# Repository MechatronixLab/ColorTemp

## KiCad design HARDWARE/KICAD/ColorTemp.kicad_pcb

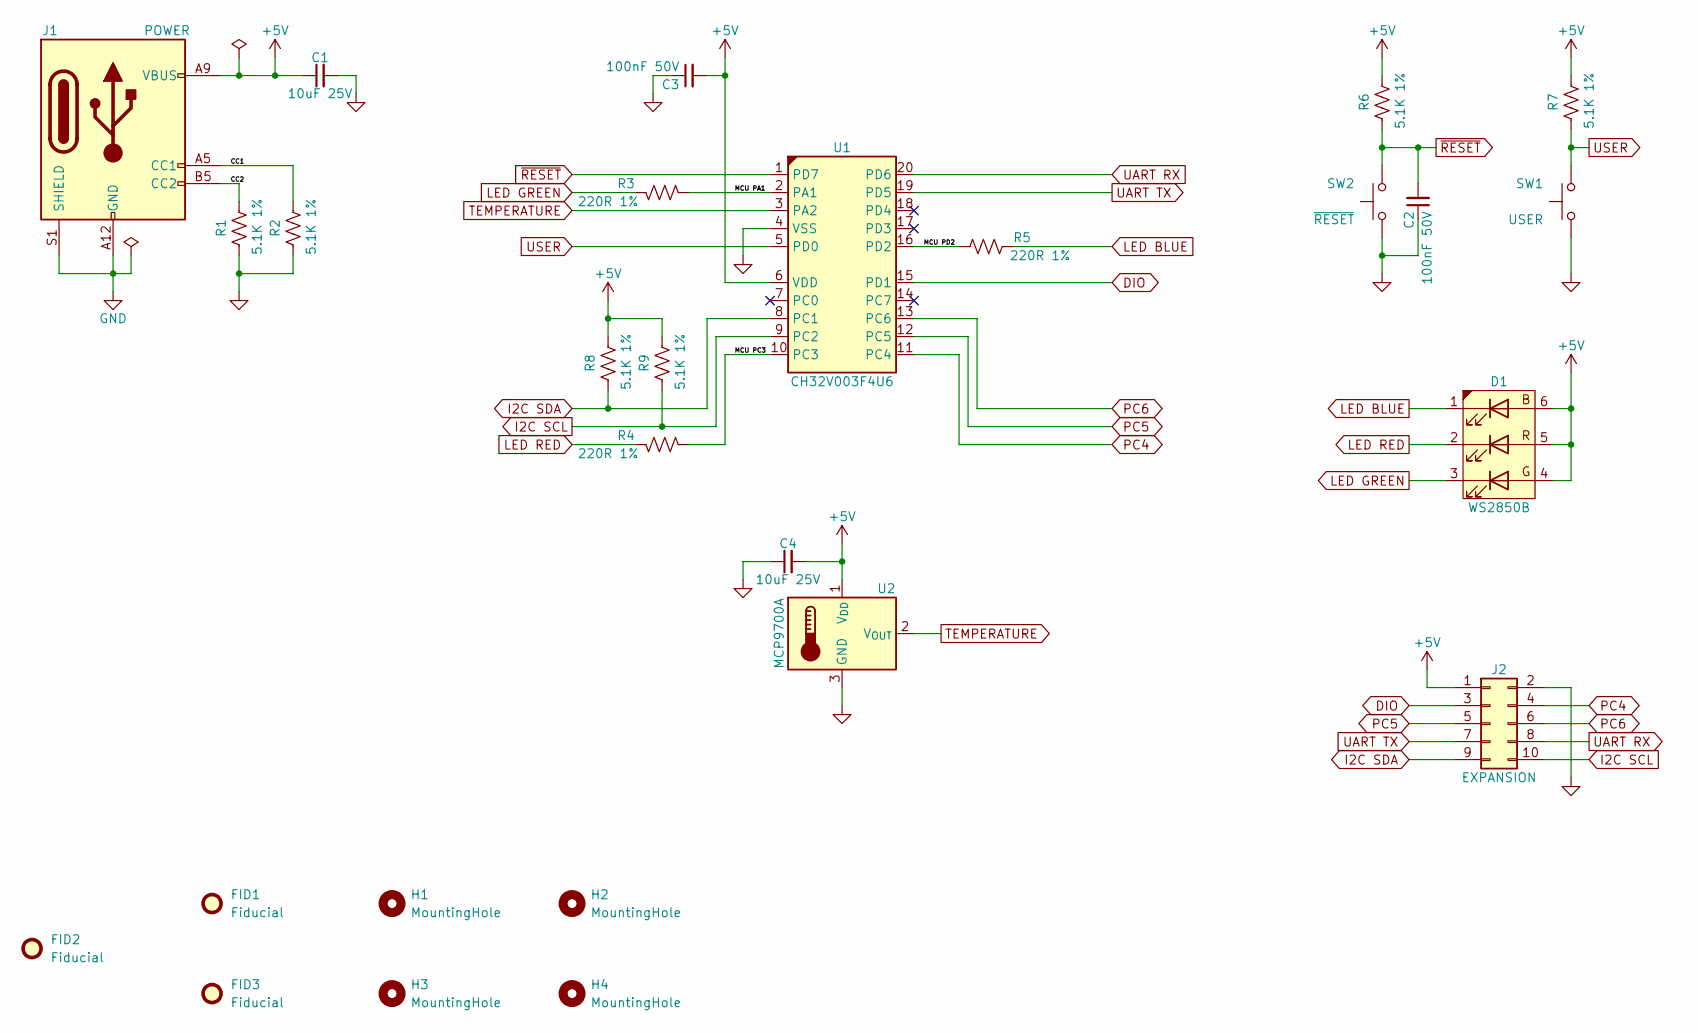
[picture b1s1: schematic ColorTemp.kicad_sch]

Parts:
C1, C4: 10uF 25V; C_0805_2012Metric; Part Number CL21A106KAYNNNE; JLCPCB C15850
C2, C3: 100nF 50V; C_0402_1005Metric; Part Number CL05B104KB54PNC; JLCPCB C307331
D1: WS2850B; Part Number WS2850B; JLCPCB C4154880
FID1, FID2, FID3: Fiducial; Fiducial_0.5mm_Mask1mm
H1, H2, H3, H4: MountingHole; MountingHole_3.2mm_M3
J1: POWER; USB_C_Receptacle_GCT_USB4125-xx-x-0190_6P_TopMnt_Horizontal; Part Number USB-TYPE-C-009; JLCPCB C2927029
J2: EXPANSION; PinHeader_2x05_P2.54mm_Vertical
R1, R2, R6, R7, R8, R9: 5.1K 1%; R_0402_1005Metric; Part Number 0402WGF5101TCE; JLCPCB C25905
R3, R4, R5: 220R 1%; R_0402_1005Metric; Part Number 0402WGF2200TCE; JLCPCB C25091
SW1: USER; EVQP7A01P; Part Number EVQP7A01P; JLCPCB C79167
SW2: ~{RESET}; EVQP7A01P; Part Number EVQP7A01P; JLCPCB C79167
U1: CH32V003F4U6; QFN-20-1EP_3x3mm_P0.4mm_EP1.65x1.65mm; Part Number CH32V003F4U6; JLCPCB C5299908
U2: MCP9700A; SOT-23; Part Number MCP9700AT-E/TT; JLCPCB C127949

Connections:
+5V: C1.1, C3.2, C4.2, D1.4 (K), D1.5 (K), D1.6 (K), J1.A9 (VBUS), J1.B9 (VBUS), J2.1, R6.1, R7.1, R8.1, R9.1, U1.6 (VDD), U2.1 (V_{DD})
/CC1: J1.A5 (CC1), R2.1
/CC2: J1.B5 (CC2), R1.1
/MCU PA1: R3.1, U1.2 (PA1)
/MCU PC3: R4.1, U1.10 (PC3)
/MCU PD2: R5.1, U1.16 (PD2)
DIO: J2.3, U1.15 (PD1)
GND: C1.2, C2.1, C3.1, C4.1, J1.A12 (GND), J1.B12 (GND), J1.S1 (SHIELD), J2.2, R1.2, R2.2, SW1.2, SW2.2, U1.4 (VSS), U1.21 (VSS), U2.3 (GND)
I2C SCL: J2.10, R9.2, U1.9 (PC2)
I2C SDA: J2.9, R8.2, U1.8 (PC1)
LED BLUE: D1.1 (A), R5.2
LED GREEN: D1.3 (A), R3.2
LED RED: D1.2 (A), R4.2
PC4: J2.4, U1.11 (PC4)
PC5: J2.5, U1.12 (PC5)
PC6: J2.6, U1.13 (PC6)
TEMPERATURE: U1.3 (PA2), U2.2 (V_{OUT})
UART RX: J2.8, U1.20 (PD6)
UART TX: J2.7, U1.19 (PD5)
USER: R7.2, SW1.1, U1.5 (PD0)
~RESET: C2.2, R6.2, SW2.1, U1.1 (PD7)

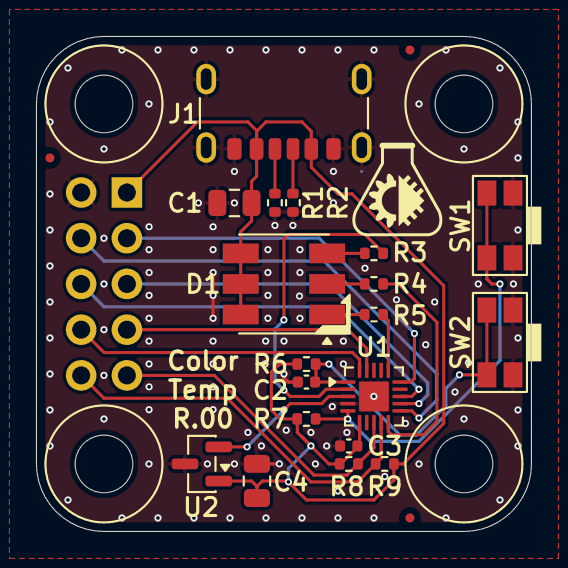
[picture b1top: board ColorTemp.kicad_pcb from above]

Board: 2 copper layers, 27.5 x 27.5 mm, 27 parts (1 on the bottom side), 21 nets.

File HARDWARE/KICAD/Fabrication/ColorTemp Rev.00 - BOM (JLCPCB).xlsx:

Comment | Designator | Footprint | JLCPCB Part # (optional)
10uF 25V | C1,C4 | C_0805_2012Metric | C15850
100nF 50V | C2,C3 | C_0402_1005Metric | C307331
WS2850B | D1 | WS2850B | C4154880
POWER | J1 | USB_C_Receptacle_GCT_USB4125-xx-x-0190_6P_TopMnt_Horizontal | C2927029
5.1K 1% | R1,R2,R6,R7,R8,R9 | R_0402_1005Metric | C25905
220R 1% | R3,R4,R5 | R_0402_1005Metric | C25091
USER | SW1 | EVQP7A01P | C79167
~{RESET} | SW2 | EVQP7A01P | C79167
CH32V003F4U6 | U1 | QFN-20-1EP_3x3mm_P0.4mm_EP1.65x1.65mm | C5299908
MCP9700A | U2 | SOT-23 | C127949

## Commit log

2026-03-01 Project creation and basic peripheral configurations.
2026-03-07 Updating .gitignore for unnecessary KiCad files.
2026-03-07 Created PCB project.
2026-03-07 Advancing on parts creation.
2026-03-09 Added most of the components. Recently project started crashing on PCB, when I press X to route. I'll try to restore a backup.
2026-03-09 Restored working project.
2026-03-09 Project restored and back to normal. Added signals to external connector.
2026-03-14 Removed transistors for driving LED. Advanced circuit and layout design. Added switches.
2026-03-14 Detailing layout and silkscreen.
2026-03-14 Preliminary PCB design done. Will now begin mechanical design.
2026-03-14 Started mechanical design.
2026-03-15 Added fiducial marks.
2026-03-15 Renumbering, PWR_FLAG, schematic detailing.
2026-03-21 Finished schematic.
2026-03-21 Fixed line widths to standardize at 0.12mm.
2026-03-21 Finished Schematic and PCB Design.
2026-03-21 Generated Gerber files and PDF.
2026-03-21 Updated gitignore to track Gerber files.
2026-03-21 Regenerated Gerber and drill files.
2026-03-21 Generated BOM and placement files. Updated detail on 220R in component library.
2026-03-21 Generated BOM and Pick and Place files.
2026-03-21 Finished project files generation for fabrication.
2026-03-21 Added QR code on PCB and links to sheets.
2026-03-21 Regenerated fabrication files after adding QR code to PCB.
2026-03-21 Had to replace de LED because it was not in Economic fabrication at JLC.
2026-03-21 Regenerated fabrication files after LED replacement.
2026-03-21 Fixed incorrect PN on 5.1K resistors.
2026-03-21 Project reviewed and uploaded to JLCPCB.
2026-03-22 Testing JLC 3DPrinting services. Added a few images.
2026-04-15 Reworked the code to work with the PCB (inverted LED logic and added temperature sensor offset).
2026-05-01 Added function to map Temperature do Color.
2026-05-02 Refactoring.
2026-05-03 Extended smooth transitions beyond -20 and +60 degrees C.
2026-05-05 Added support for used button.
2026-05-05 Added mode selection and LED sweep. Needs refactoring.
